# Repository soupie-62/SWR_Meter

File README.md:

# SWR_Meter
Notes on an SWR meter. Directional coupler PCB

If you want to truly understand something, try building it. In this, I'm trying to understand directional couplers, as used in SWR meters.

The most basic version is a "sensor" track, very close to the main PCB track. This is only good when the length of track is a significant portion of frequency wavelength.
You could make the PCB longer, but the size limit for cheap PCBs is 10cm x 10cm (4 inch x 4 inch old scale).

At lower frequencies, the "stockton" circuit uses toroid transformers to sense the source voltage and current. The frequency range becomes a function of the toroids used.

My circuit:
I want to create coils from PCB tracks, keeping the Stockton design but eliminating the toroidal transformers.

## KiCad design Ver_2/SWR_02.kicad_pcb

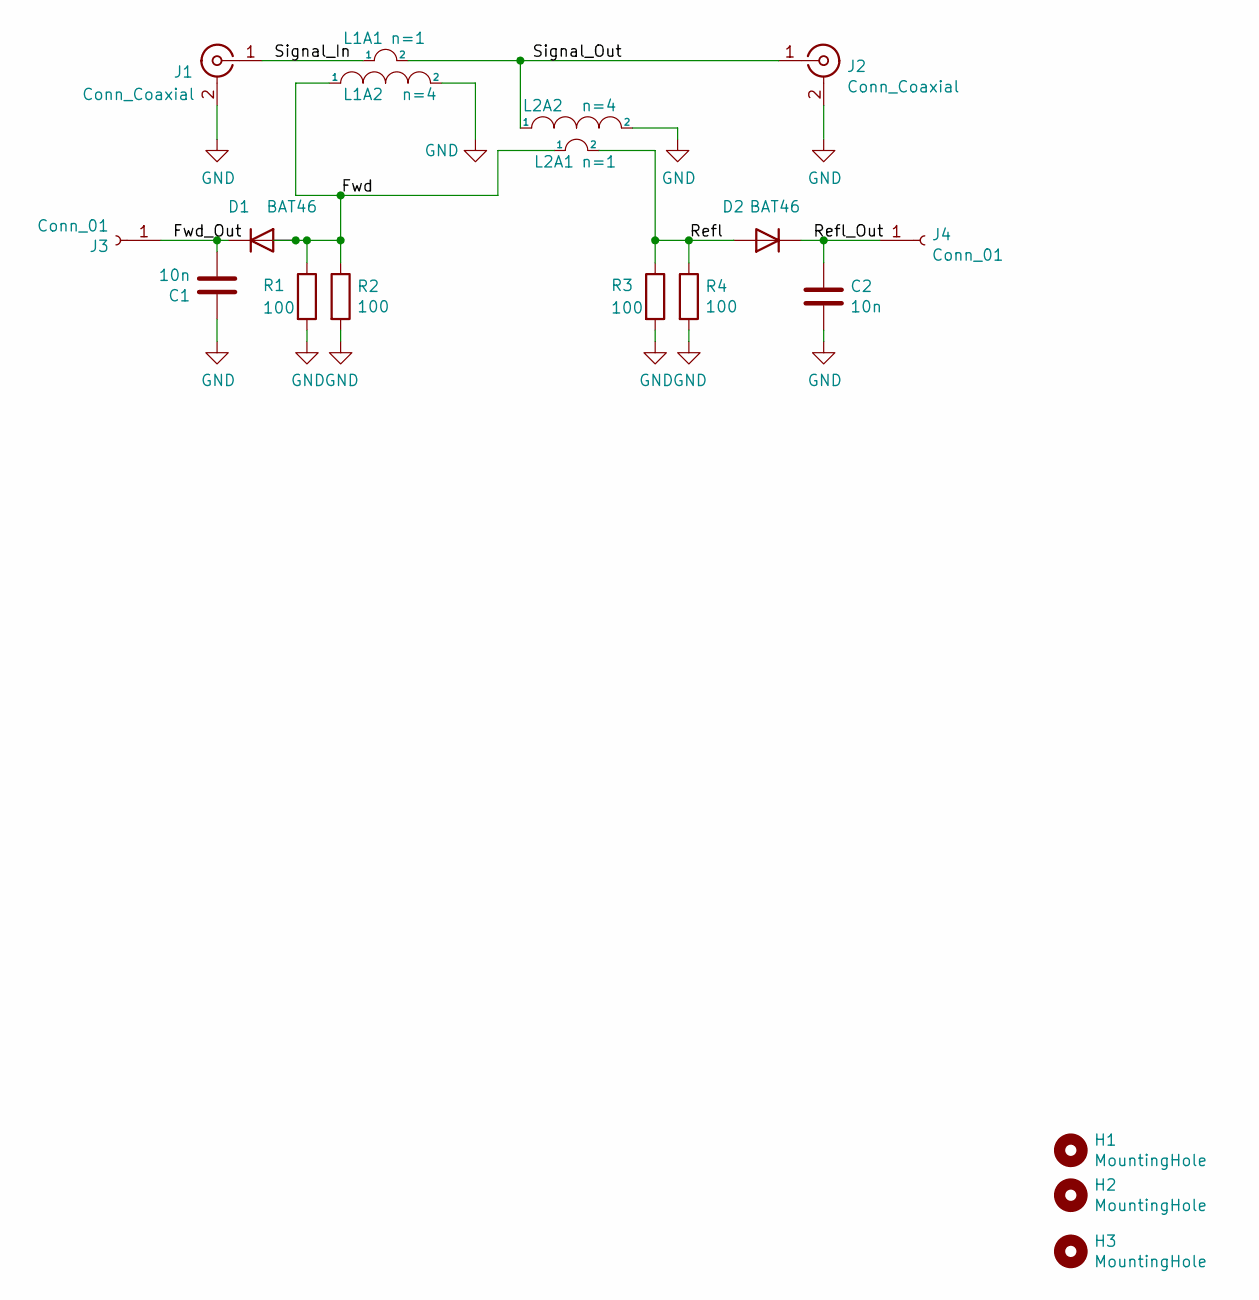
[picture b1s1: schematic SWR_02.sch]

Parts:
C1, C2: 10n; C_1812_4532Metric_Pad1.57x3.40mm_HandSolder
D1, D2: BAT46; D_SOD-123
H1, H2, H3: MountingHole; MountingHole_2.5mm_Pad_TopBottom
J1, J2: Conn_Coaxial; BNC_Custom_01_SMT
J3, J4: Conn_01; SolderWire-0.75sqmm_1x01_D1.25mm_OD2.3mm
L1A1, L2A1: n=1; Coil_PCB_85mil
L1A2, L2A2: n=4; Coil_PCB_85mil
R1, R2, R3, R4: 100; R_2010_5025Metric_HandSolder

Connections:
/Fwd: D1.2 (A), L1A2.1, L2A1.1, R1.1, R2.1
/Fwd_Out: C1.2, D1.1 (K), J3.1
/Refl: D2.2 (A), L2A1.2, R3.1, R4.1
/Refl_Out: C2.1, D2.1 (K), J4.1
/Signal_In: J1.1 (In), L1A1.1
/Signal_Out: J2.1 (In), L1A1.2, L2A2.1
GND: C1.1, C2.2, J1.2 (Ext), J2.2 (Ext), L1A2.2, L2A2.2, R1.2, R2.2, R3.2, R4.2

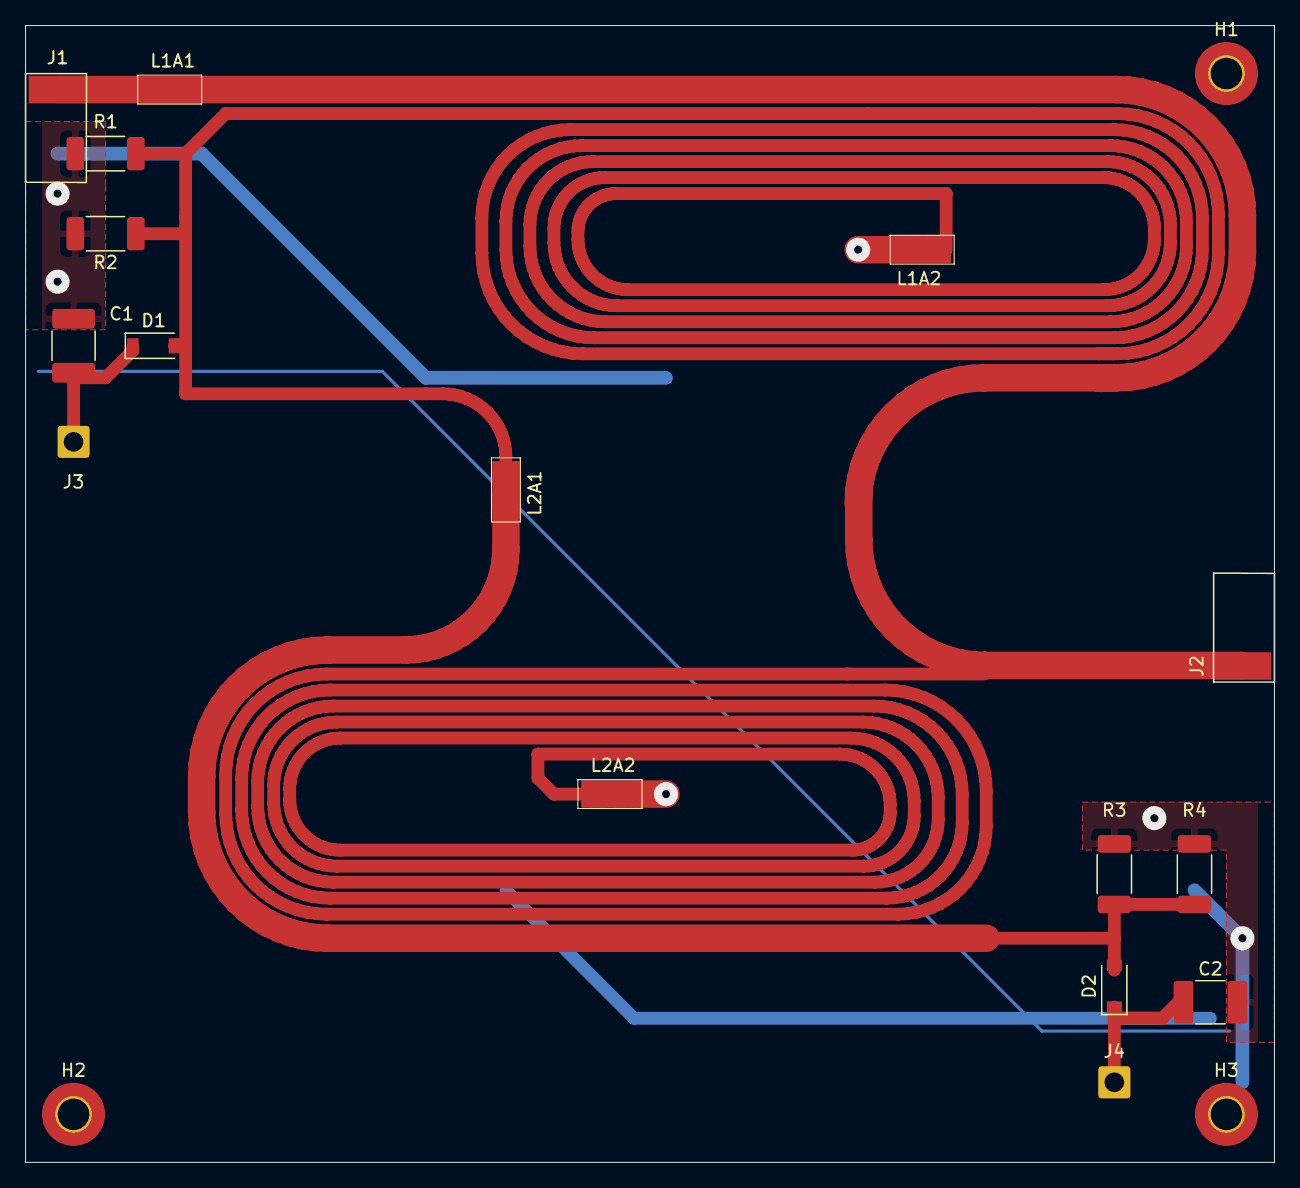
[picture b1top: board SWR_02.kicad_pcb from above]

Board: 2 copper layers, 99.1 x 90.2 mm, 19 parts (0 on the bottom side), 7 nets.

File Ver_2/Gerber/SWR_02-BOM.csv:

Comment,Designator,Footprint,JLCPCB Part #?optional?
Conn_Coaxial,J1,,
Conn_Coaxial,J2,,
100 Ohm,R1,2010 SMD,C50472
100 Ohm,R2,2010 SMD,C50472
100 Ohm,R3,2010 SMD,C50472
100 Ohm,R4,2010 SMD,C50472
10nF,C1,1812 SMD,C426626
10nF,C2,1812 SMD,C426626
BAT46,D2,SOD123,C283255
BAT46,D1,SOD123,C283255
Conn_01x01_Female,J4,,
Conn_01x01_Female,J3,,

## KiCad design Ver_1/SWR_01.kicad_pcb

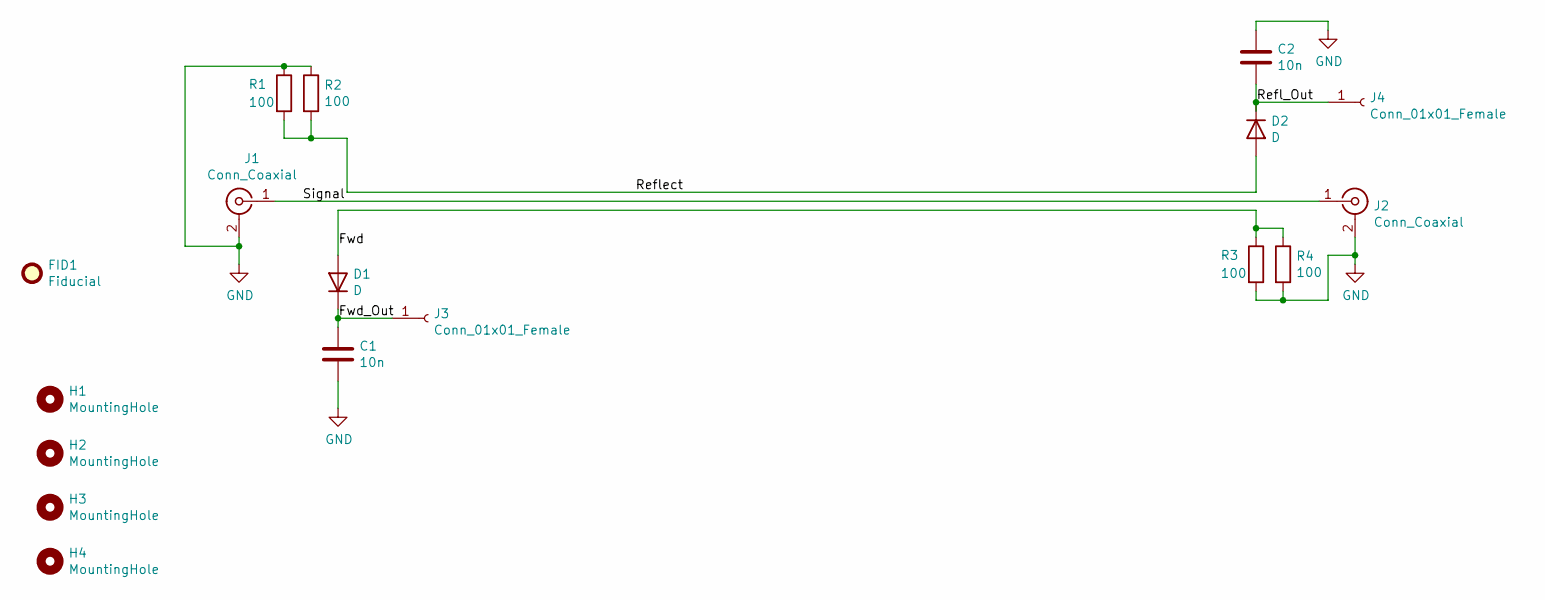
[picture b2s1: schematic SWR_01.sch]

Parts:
C1, C2: 10n; C_1812_4532Metric_Pad1.57x3.40mm_HandSolder
D1, D2: D; D_1812_4532Metric_Pad1.30x3.40mm_HandSolder
FID1: Fiducial; Fiducial_0.5mm_Mask1.5mm
H1, H2, H3, H4: MountingHole; MountingHole_2.5mm_Pad_TopBottom
J1, J2: Conn_Coaxial; BNC_Custom_01_SMT
J3, J4: Conn_01x01_Female; SolderWire-2sqmm_1
R1, R2, R3, R4: 100; R_2010_5025Metric_HandSolder

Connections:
/Fwd: D1.2 (A), R3.1, R4.1
/Fwd_Out: C1.1, D1.1 (K), J3.1
/Refl_Out: C2.2, D2.1 (K), J4.1
/Reflect: D2.2 (A), R1.2, R2.2
/Signal: J1.1 (In), J2.1 (In)
GND: C1.2, C2.1, J1.2 (Ext), J2.2 (Ext), R1.1, R2.1, R3.2, R4.2

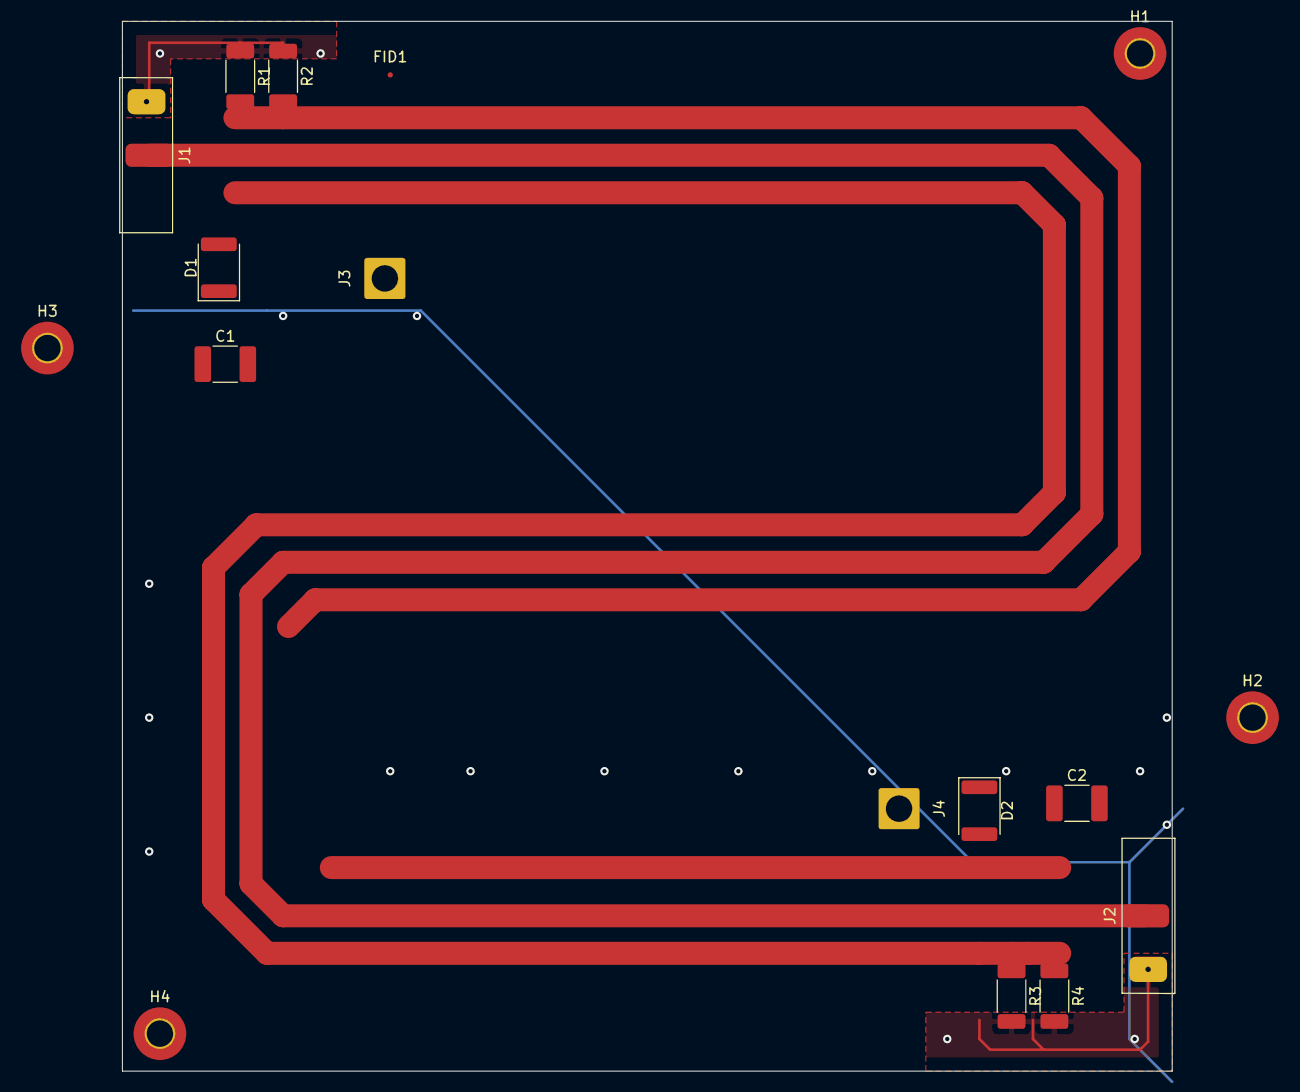
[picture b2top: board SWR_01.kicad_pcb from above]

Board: 2 copper layers, 99.6 x 99.6 mm, 17 parts (0 on the bottom side), 6 nets.

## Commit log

2021-11-28 Notes subdirectory create
2021-11-28 Update Readme
    Source of PCB Spiral image
2021-11-28 Create Ver_1
    Kicad files for version 1 go here
2021-11-28 Add files via upload
    Kicad files added
2021-11-29 Update README.md
    Added PCB Image
2021-11-29 Create dummy
2021-11-29 Add files via upload
    Version 2 has curved tracks
2021-12-02 Delete Ver_1 directory
    Removed old version 1
2021-12-02 Add files via upload
    Version 1 now in Zip archive
2021-12-02 Add files via upload
    Updated files copied to Git
2021-12-02 Add files via upload
    Updated Gerber plots
2021-12-02 Add files via upload
    Updated notes include datasheets for BOM
2021-12-07 Add files via upload
    S-Parameter modelling
